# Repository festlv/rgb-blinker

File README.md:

rgb-blinker
===========

RGB LED blinker with Atmel ATTiny85/13- PCB and schematics.
PCB layout and schematics were done in KiCad.

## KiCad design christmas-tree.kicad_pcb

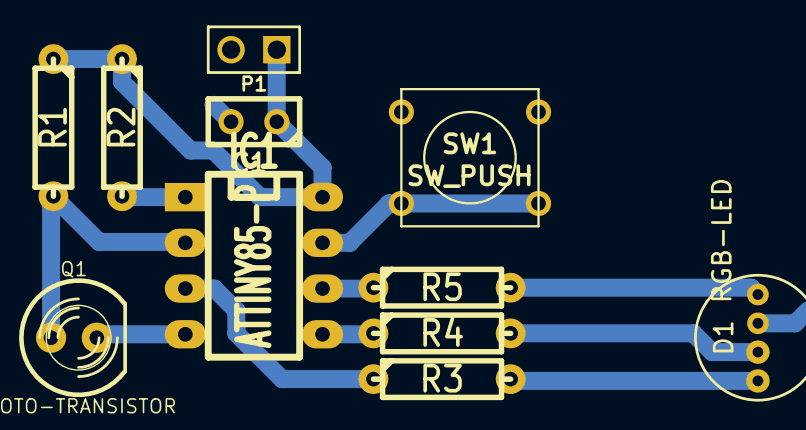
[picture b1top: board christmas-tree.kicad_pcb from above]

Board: 2 copper layers, 11 parts (0 on the bottom side), 11 nets.

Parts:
C1: 1uF; C1
D1: RGB-LED
IC1: ATTINY85-P; DIP-8__300_ELL
P1: CONN_2; PIN_ARRAY_2X1
Q1: PHOTO-TRANSISTOR; LED-5MM
R1: 50K; R3-LARGE_PADS
R2: 10K; R3-LARGE_PADS
R3, R4, R5: R; R3-LARGE_PADS
SW1: SW_PUSH; SW_PUSH_SMALL

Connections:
GND: C1.2, D1.3, IC1.4, P1.2, Q1.2, SW1.1
unnamed: IC1.5, R4.1
unnamed: IC1.6, R5.1
unnamed: IC1.3, R3.1
unnamed: D1.4, R5.2
unnamed: D1.2, R4.2
unnamed: D1.1, R3.2
unnamed: IC1.2, Q1.1, R1.2
unnamed: IC1.7, SW1.2
unnamed: IC1.1, R2.2
VCC: C1.1, IC1.8, P1.1, R1.1, R2.1

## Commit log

2014-12-19 Changes from workstation
2014-12-19 Changed switch, PCB layout
2014-12-19 Added output files
2014-12-19 Latest version
2014-12-19 Updated PCB to latest version as well
